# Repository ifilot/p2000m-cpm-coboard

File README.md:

# P2000M CP/M co-board

This board adds the memory mapping and local RAM needed to run CP/M on a
Philips P2000M. It sits between the CPU board and the video expansion board
and replaces the motherboard's 82S123 address-decoder PROM.

## Features

- An ATF1502AS CPLD recreates the stock P2000M decode after reset and switches
  to the CP/M map when software writes `80h` to a port in `20h`-`2Fh`.
- A 128 KiB CY62128 SRAM supplies the fixed 16 KiB CP/M bank and seven optional
  16 KiB banks. The tested CUPL implementation supports the complete banked
  interface described below.
- The two 40-pin connectors pass the CPU and video-expansion buses through the
  co-board. The 16-pin plug replaces the motherboard's 82S123 PROM.
- The CPLD's JTAG pins remain available for programming.

The normal CP/M map is:

| Address range | Function |
| --- | --- |
| `0000`-`3FFF` | Motherboard RAM |
| `4000`-`9FFF` | 24 KiB RAM on the floppy-controller board |
| `A000`-`DFFF` | Co-board SRAM, fixed bank 0 |
| `E000`-`EFFF` | CP/M cartridge BIOS slice |
| `F000`-`FFFF` | Video and attributes |

The opening below the CPU-board connector clears the mating connector and
surrounding hardware, allowing the co-board to fit in the existing stack.

## Installation

Work with the P2000M powered off. Remove the original 82S123 PROM and install
the co-board's 16-pin plug in that socket with pin 1 correctly aligned. Connect
the CPU-board and video-expansion-board headers to their matching co-board
connectors.

<table>
  <tr>
    <td width="50%"><br><em>Top view of the installed co-board.</em></td>
    <td width="50%"><br><em>Side view of the board stack.</em></td>
  </tr>
</table>

Program the CPLD with the tested
[`cupl/p2000m-cpm-coboard.jed`](cupl/p2000m-cpm-coboard.jed). Its matching
source is [`cupl/p2000m-cpm-coboard.pld`](cupl/p2000m-cpm-coboard.pld).
Programming and verification details are in [`cupl/README.md`](cupl/README.md).
The CP/M cartridge and disk images are in [`software`](software).

> [!NOTE]
> The open-source [ATF150x Programmer](https://github.com/ifilot/atf150x-programmer)
> can flash the CPLD without the comparatively expensive proprietary programmer.

## Systems without the floppy-controller board

The optional `no-floppy` CUPL variant replaces the absent board's 24 KiB RAM
during CP/M operation. It is intended only for a machine in which the complete
floppy-controller board is physically absent. It does not emulate the floppy
controller or provide disk storage.

That variant allocates onboard SRAM as follows:

| SRAM bank | Use |
| --- | --- |
| 0 | Fixed CP/M RAM at `A000`-`DFFF` |
| 1 | Replacement RAM at `4000`-`7FFF` |
| 2, lower 8 KiB | Replacement RAM at `8000`-`9FFF` |
| 3-7 | Optional 16 KiB banks at `4000`-`7FFF` |

It therefore exposes five optional banks rather than seven. This variant only
replaces RAM in CP/M mode; it does not provide the stock-map expansion RAM at
`A000`-`FFFF`. See [`cupl/README.md`](cupl/README.md) before using it.

The compiled [`p2000m-cpm-coboard-no-floppy.jed`](cupl/p2000m-cpm-coboard-no-floppy.jed)
is included because building it requires WinCUPL. It has passed source
verification and ATF1502AS fitting, but still requires testing on physical
hardware.

## Licence

The canonical co-board hardware and associated CUPL source are released under
the [CERN Open Hardware Licence Version 2 — Permissive
(CERN-OHL-P-2.0)](https://ohwr.org/cern_ohl_p_v2.txt).

Files that identify another licence, and third-party or historical materials
under `literature` and `archive`, retain their own terms.

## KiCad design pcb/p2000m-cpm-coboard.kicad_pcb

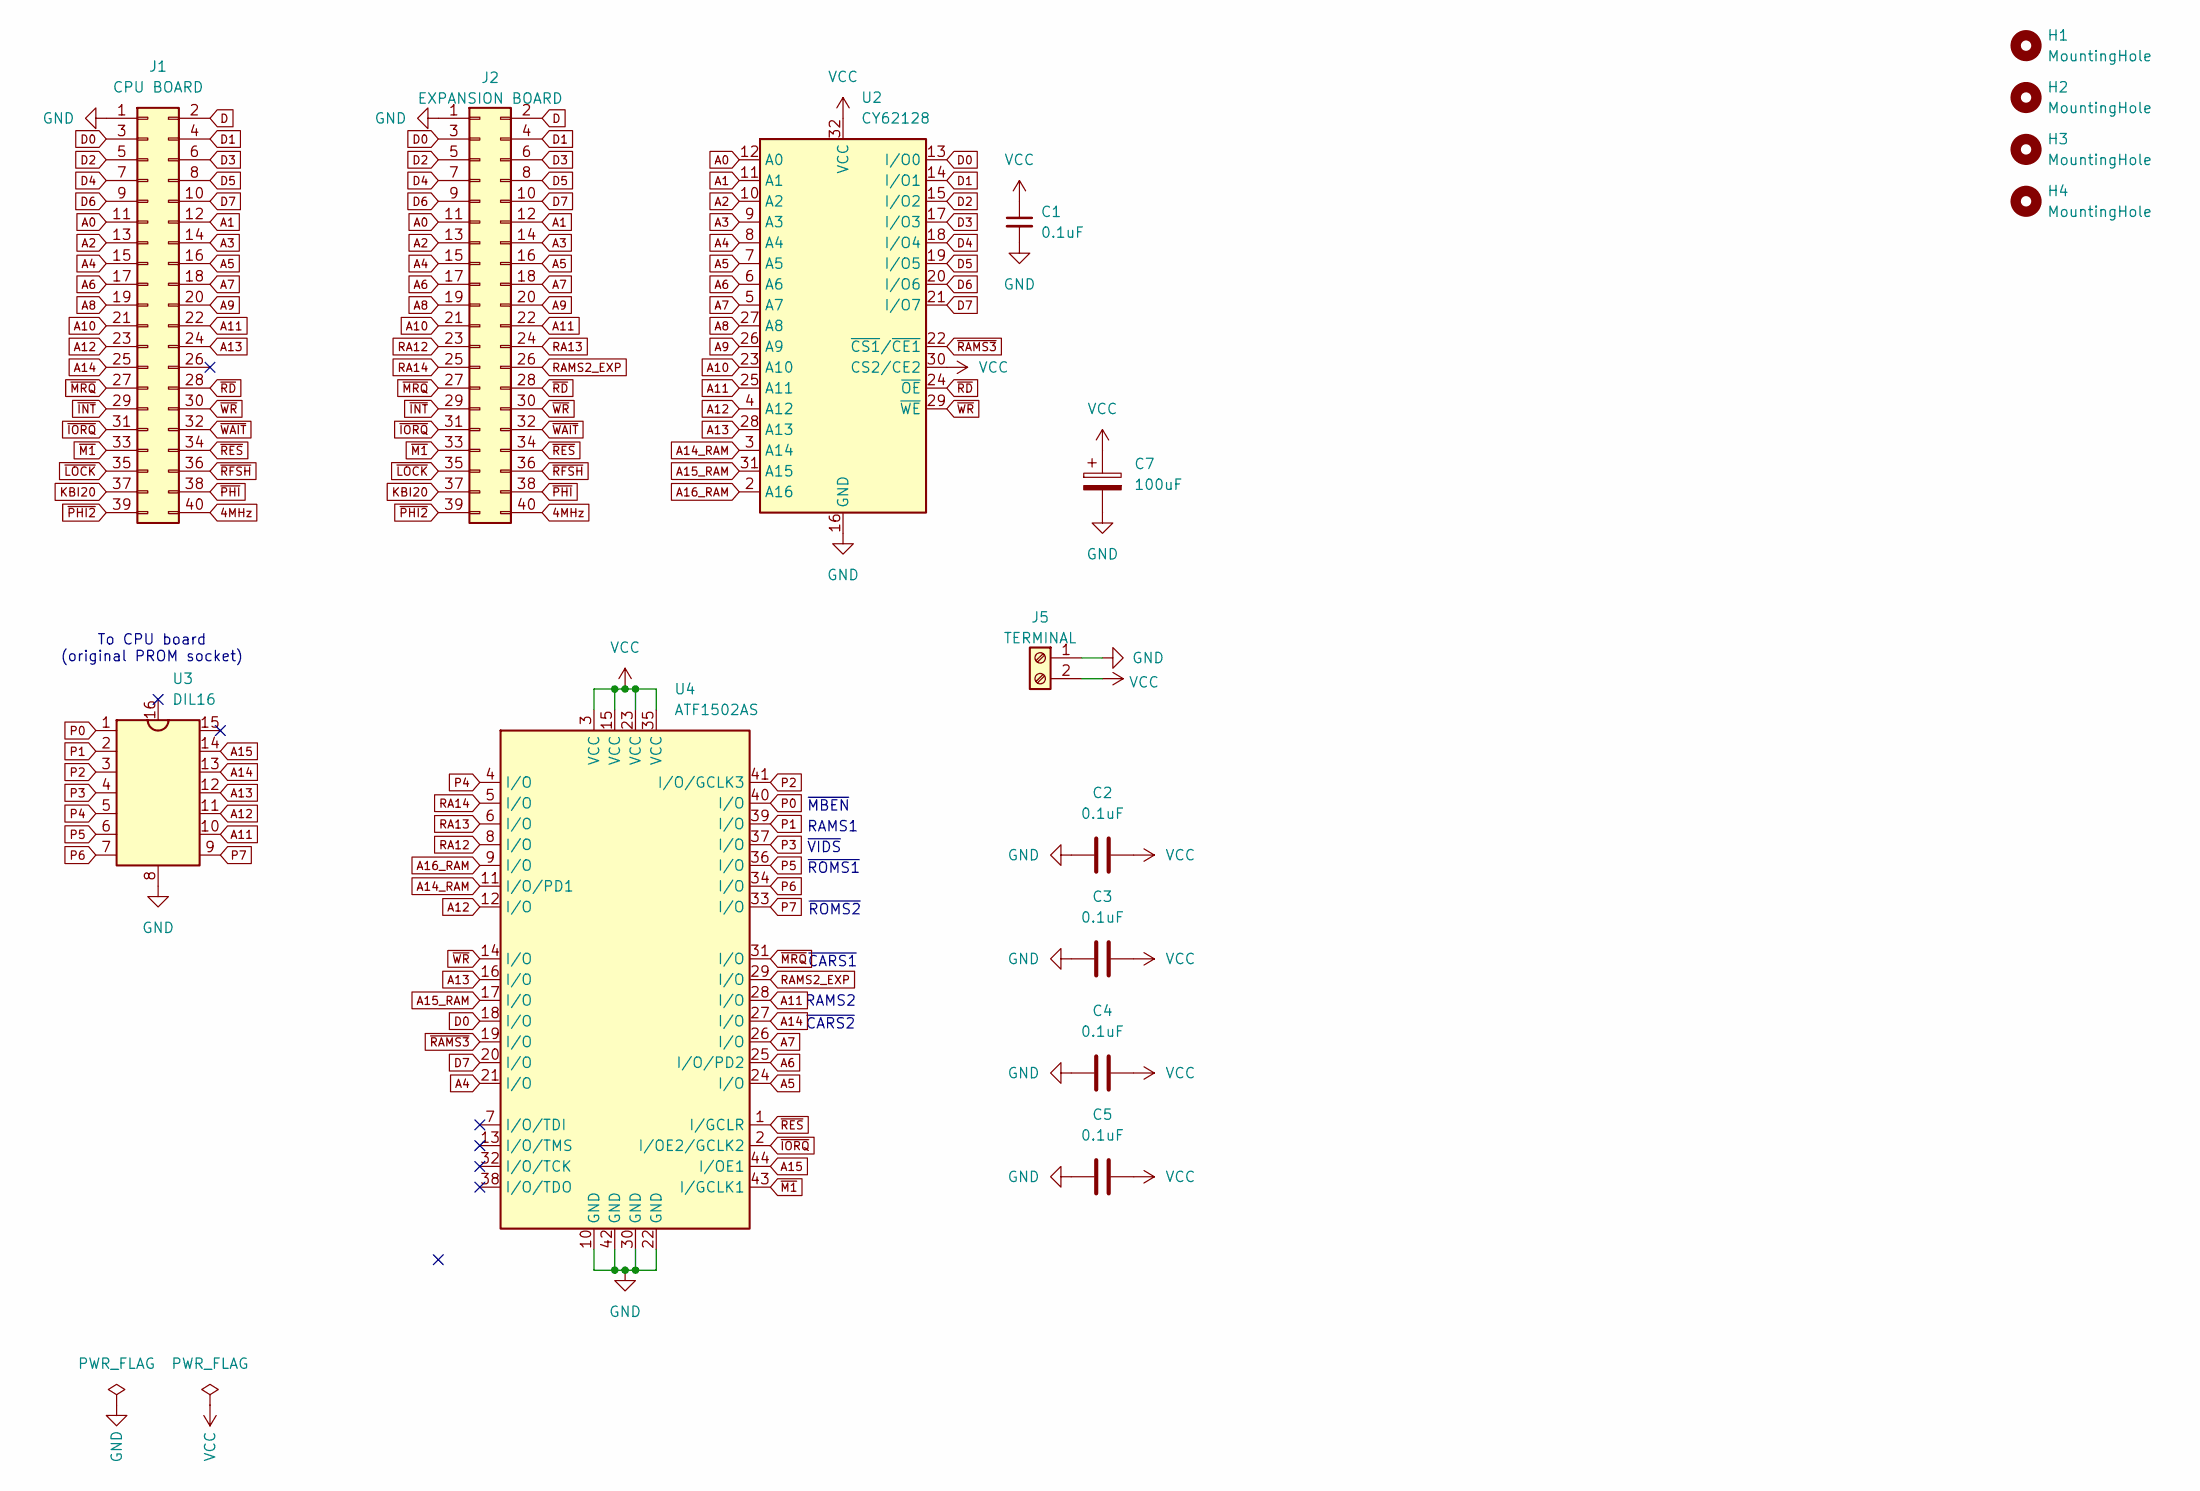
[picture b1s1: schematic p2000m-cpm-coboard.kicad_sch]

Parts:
C1, C2, C3, C4, C5: 0.1uF; C_0805_2012Metric_Pad1.18x1.45mm_HandSolder
C7: 100uF; CP_Radial_D6.3mm_P2.50mm
H1, H2, H3, H4: MountingHole; MountingHole_3.2mm_M3_Pad_Via
J1: CPU BOARD; PinHeader_2x20_P2.54mm_Vertical
J2: EXPANSION BOARD; PinHeader_2x20_P2.54mm_Vertical
J5: TERMINAL; TerminalBlock_RND_205-00232_1x02_P5.08mm_Horizontal
U2: CY62128; SOP-32_11.305x20.495mm_P1.27mm
U3: DIL16; DIP-16_W7.62mm_Socket
U4: ATF1502AS; PLCC-44_THT-Socket

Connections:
4MHz: J1.40, J2.40
A0: J1.11, J2.11, U2.12 (A0)
A1: J1.12, J2.12, U2.11 (A1)
A2: J1.13, J2.13, U2.10 (A2)
A3: J1.14, J2.14, U2.9 (A3)
A4: J1.15, J2.15, U2.8 (A4), U4.21 (I/O)
A5: J1.16, J2.16, U2.7 (A5), U4.24 (I/O)
A6: J1.17, J2.17, U2.6 (A6), U4.25 (I/O/PD2)
A7: J1.18, J2.18, U2.5 (A7), U4.26 (I/O)
A8: J1.19, J2.19, U2.27 (A8)
A9: J1.20, J2.20, U2.26 (A9)
A10: J1.21, J2.21, U2.23 (A10)
A11: J1.22, J2.22, U2.25 (A11), U3.10, U4.28 (I/O)
A12: J1.23, U2.4 (A12), U3.11, U4.12 (I/O)
A13: J1.24, U2.28 (A13), U3.12, U4.16 (I/O)
A14: J1.25, U3.13, U4.27 (I/O)
A14_RAM: U2.3 (A14), U4.11 (I/O/PD1)
A15: U3.14, U4.44 (I/OE1)
A15_RAM: U2.31 (A15), U4.17 (I/O)
A16_RAM: U2.2 (A16), U4.9 (I/O)
D: J1.2, J2.2
D0: J1.3, J2.3, U2.13 (I/O0), U4.18 (I/O)
D1: J1.4, J2.4, U2.14 (I/O1)
D2: J1.5, J2.5, U2.15 (I/O2)
D3: J1.6, J2.6, U2.17 (I/O3)
D4: J1.7, J2.7, U2.18 (I/O4)
D5: J1.8, J2.8, U2.19 (I/O5)
D6: J1.9, J2.9, U2.20 (I/O6)
D7: J1.10, J2.10, U2.21 (I/O7), U4.20 (I/O)
GND: C1.2, C2.2, C3.2, C4.2, C5.2, C7.2, J1.1, J2.1, J5.1, U2.16 (GND), U3.8, U4.10 (GND), U4.22 (GND), U4.30 (GND), U4.42 (GND)
KBI20: J1.37, J2.37
P0: U3.1, U4.40 (I/O)
P1: U3.2, U4.39 (I/O)
P2: U3.3, U4.41 (I/O/GCLK3)
P3: U3.4, U4.37 (I/O)
P4: U3.5, U4.4 (I/O)
P5: U3.6, U4.36 (I/O)
P6: U3.7, U4.34 (I/O)
P7: U3.9, U4.33 (I/O)
RA12: J2.23, U4.8 (I/O)
RA13: J2.24, U4.6 (I/O)
RA14: J2.25, U4.5 (I/O)
RAMS2_EXP: J2.26, U4.29 (I/O)
VCC: C1.1, C2.1, C3.1, C4.1, C5.1, C7.1, J5.2, U2.30 (CS2/CE2), U2.32 (VCC), U4.3 (VCC), U4.15 (VCC), U4.23 (VCC), U4.35 (VCC)
~INT: J1.29, J2.29
~IORQ: J1.31, J2.31, U4.2 (I/OE2/GCLK2)
~LOCK: J1.35, J2.35
~M1: J1.33, J2.33, U4.43 (I/GCLK1)
~MRQ: J1.27, J2.27, U4.31 (I/O)
~PHI2: J1.39, J2.39
~PHI: J1.38, J2.38
~RAMS3: U2.22 (~CS1/~CE1), U4.19 (I/O)
~RD: J1.28, J2.28, U2.24 (~OE)
~RES: J1.34, J2.34, U4.1 (I/GCLR)
~RFSH: J1.36, J2.36
~WAIT: J1.32, J2.32
~WR: J1.30, J2.30, U2.29 (~WE), U4.14 (I/O)

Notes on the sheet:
~{CARS1}
~{ROMS1}
~{MBEN}
~{CARS2}
RAMS2
RAMS1
To CPU board (original PROM socket)
~{ROMS2}
~{VIDS}

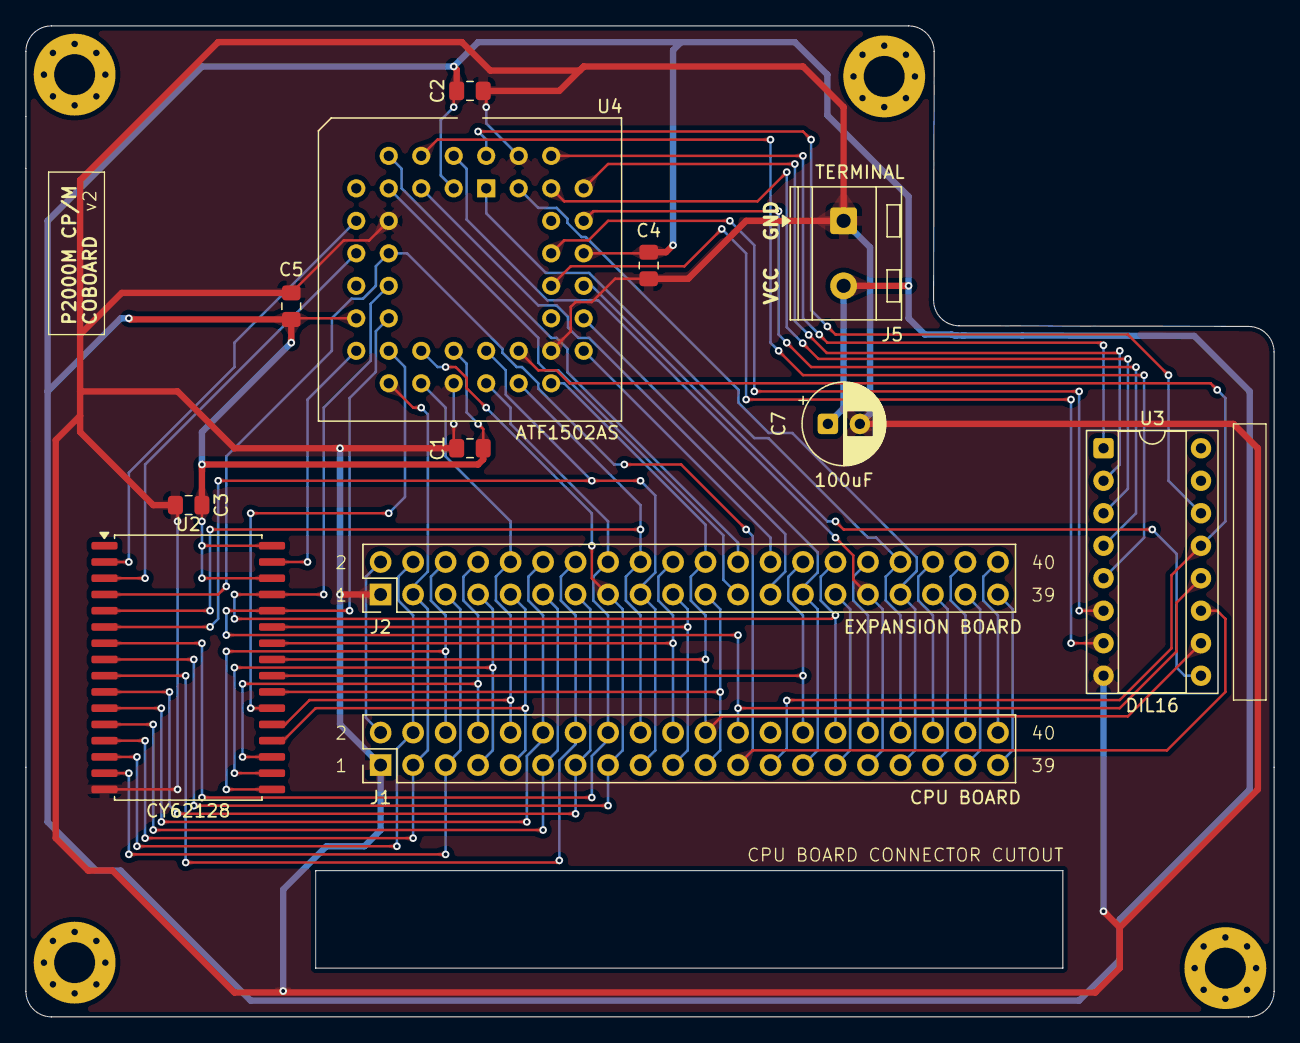
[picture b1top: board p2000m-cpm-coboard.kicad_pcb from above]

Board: 2 copper layers, 97.6 x 77.5 mm, 16 parts (0 on the bottom side), 57 nets.
